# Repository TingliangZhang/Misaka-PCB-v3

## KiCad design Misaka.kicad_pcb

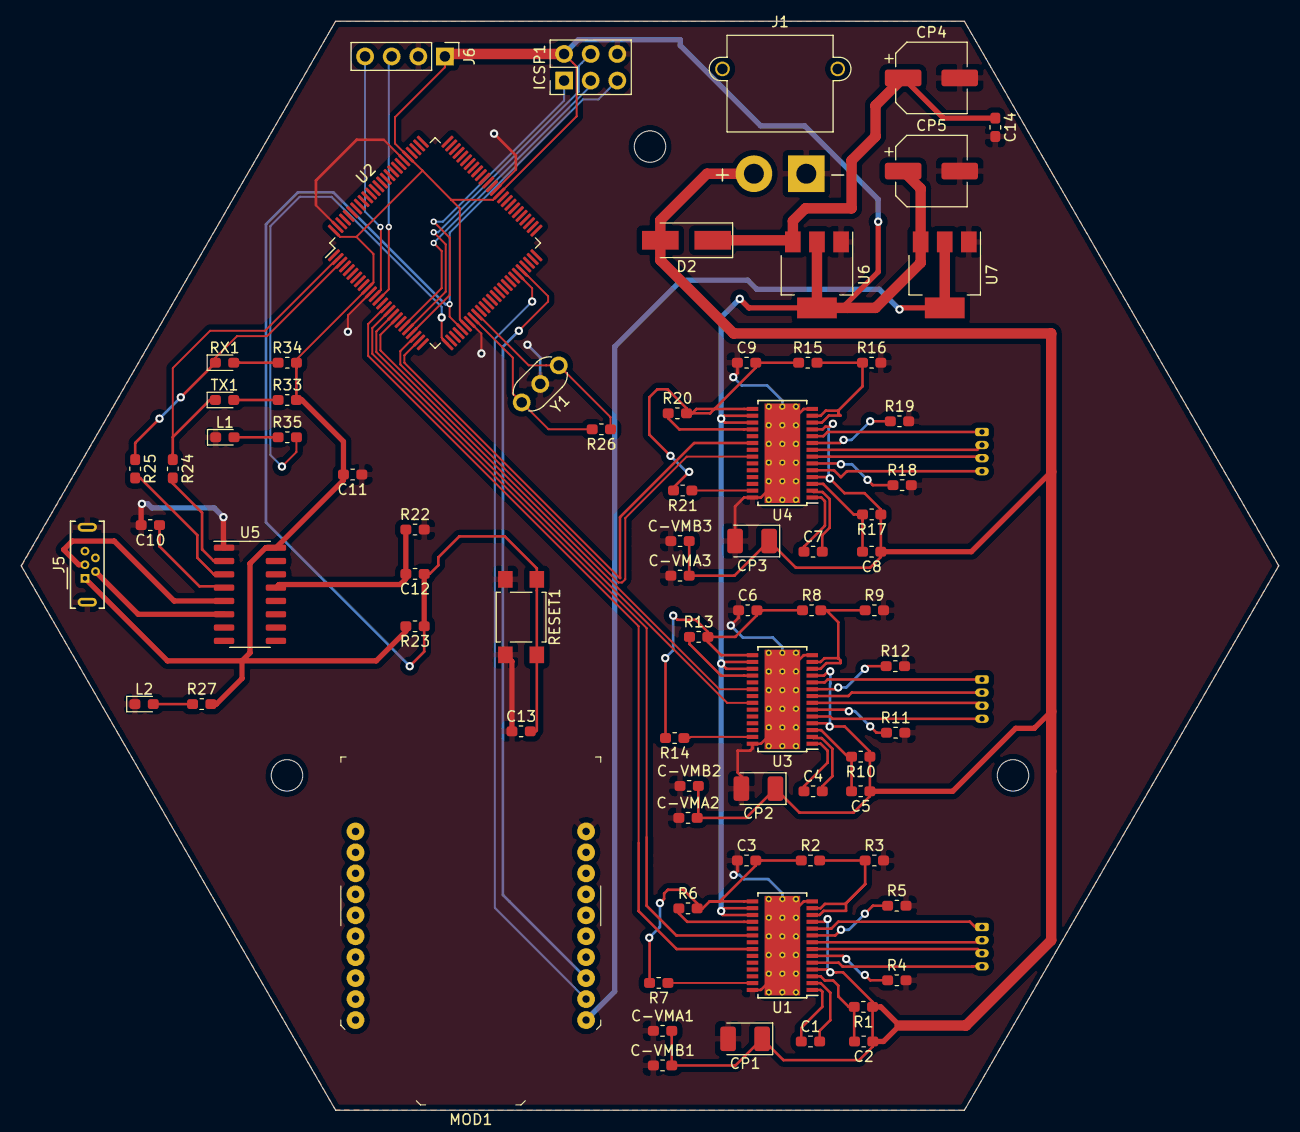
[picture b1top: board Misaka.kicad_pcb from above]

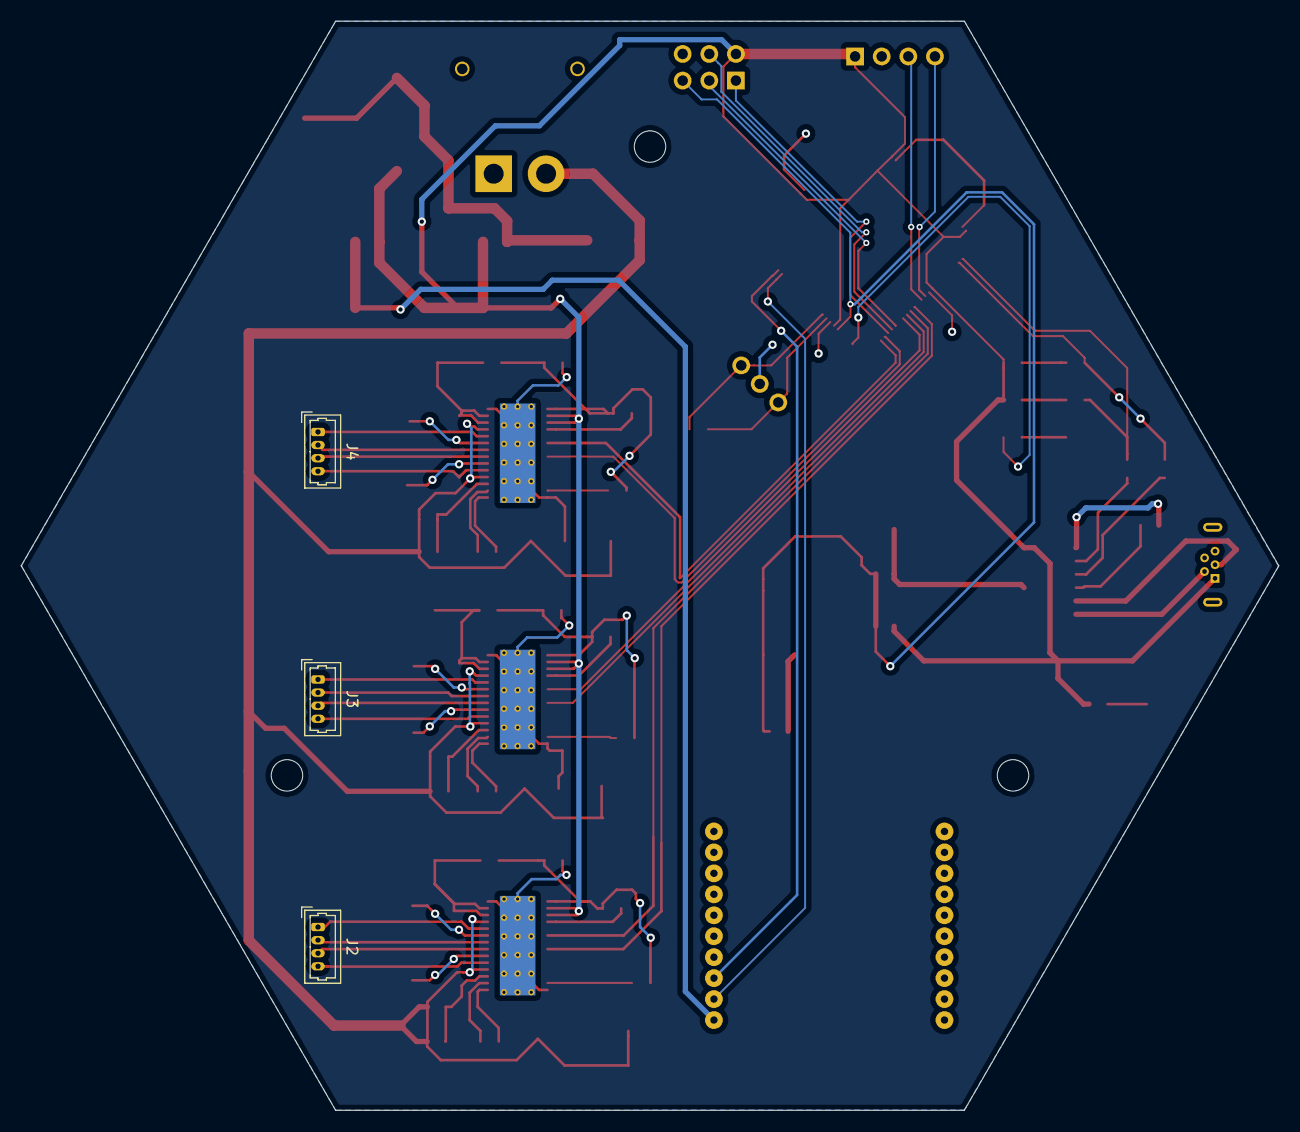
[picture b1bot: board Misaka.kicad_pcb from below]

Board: 2 copper layers, 120.0 x 103.9 mm, 77 parts (3 on the bottom side), 73 nets.

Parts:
C1, C4, C7: 0.01uF; C_0603_1608Metric_Pad1.05x0.95mm_HandSolder
C2, C5, C8: 0.1uF; C_0603_1608Metric_Pad1.05x0.95mm_HandSolder
C3, C6, C9: 0.47uF; C_0603_1608Metric_Pad1.05x0.95mm_HandSolder
C10, C11, C12, C14: 100nF; C_0603_1608Metric_Pad1.05x0.95mm_HandSolder
C13: 22pF; C_0603_1608Metric_Pad1.05x0.95mm_HandSolder
C-VMA1, C-VMA2, C-VMA3: 0.1uF; C_0603_1608Metric_Pad1.05x0.95mm_HandSolder
C-VMB1, C-VMB2, C-VMB3: 0.1uF; C_0603_1608Metric_Pad1.05x0.95mm_HandSolder
CP1, CP2, CP3: 100uF; CP_EIA-3528-21_Kemet-B_Pad1.50x2.35mm_HandSolder
CP4, CP5: 47uF; CP_Elec_6.3x5.8
D2: M7; D_SMA_Handsoldering
ICSP1: Conn_02x03_Odd_Even; PinHeader_2x03_P2.54mm_Vertical
J1: Battery; AMASS_XT30PW-M_1x02_P2.50mm_Horizontal
J2, J3, J4: Conn_01x04_Male; Molex_PicoBlade_53047-0410_1x04_P1.25mm_Vertical
J5: USB_B_Micro; USB_Micro-B_Wuerth_614105150721_Vertical
J6: Conn_01x04_Female; PinHeader_1x04_P2.54mm_Vertical
L1, L2: LED; LED_0603_1608Metric_Pad1.05x0.95mm_HandSolder
MOD1: XB24CZ7PIT-004; XBEE_PRO-20_THT
R1, R10, R17, R26: 1M; R_0603_1608Metric_Pad1.05x0.95mm_HandSolder
R2, R8, R15: 50K; R_0603_1608Metric_Pad1.05x0.95mm_HandSolder
R3, R9, R16: 30K; R_0603_1608Metric_Pad1.05x0.95mm_HandSolder
R4, R5, R11, R12, R18, R19: 200m; R_0603_1608Metric_Pad1.05x0.95mm_HandSolder
R6, R7, R13, R14, R20, R21: 10K; R_0603_1608Metric_Pad1.05x0.95mm_HandSolder
R22, R24, R25, R27, R33, R34, R35: 1k; R_0603_1608Metric_Pad1.05x0.95mm_HandSolder
R23: 10k; R_0603_1608Metric_Pad1.05x0.95mm_HandSolder
RESET1: SW_Push; SW_SPST_TL3305A
RX1: LED; LED_0603_1608Metric_Pad1.05x0.95mm_HandSolder
TX1: LED; LED_0603_1608Metric_Pad1.05x0.95mm_HandSolder
U1, U3, U4: DRV8825PWPR; HTSSOP-28-1EP_4.4x9.7mm_P0.65mm_EP3.4x9.5mm_ThermalVias
U2: ATmega2560-16AU; TQFP-100_14x14mm_P0.5mm
U5: CH340C; SOIC-16_3.9x9.9mm_P1.27mm
U6: AMS1117-5.0; SOT-223-3_TabPin2
U7: AMS1117-3.3; SOT-223-3_TabPin2
Y1: CSTLS16M0X51-B0; Resonator_muRata_CSTLSxxxX-3Pin_W5.5mm_H3.0mm

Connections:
+3V3: MOD1.1, U7.2
+5V: C11.2, CP5.1, ICSP1.2, J5.1, J6.1, R23.2, R27.2, R33.2, R34.2, U1.16, U1.17, U2.10, U2.31, U2.61, U2.80, U2.100, U3.16, U3.17, U4.16, U4.17, U5.16, U6.2, U7.3
+12V: C2.1, C5.1, C8.1, C-VMA1.2, C-VMA2.2, C-VMA3.2, C-VMB1.2, C-VMB2.2, C-VMB3.2, CP1.1, CP2.1, CP3.1, D2.2, J1.2, R1.1, R10.1, R17.1, U1.4, U1.11, U3.4, U3.11, U4.4, U4.11
/D6: U1.22, U2.15
/D7: U1.20, U2.16
/D8: U2.17, U3.22
/D9: U2.18, U3.20
/D10: U2.23, U4.22
/D11: U2.24, U4.20
/D13: R35.2, U2.26
/MISO: ICSP1.1, U2.22
/MOSI: ICSP1.4, U2.21
/RESET: C12.1, C13.2, ICSP1.5, R23.1, RESET1.1, U2.30
/RX0: R24.1, TX1.1, U2.2
/RX1: MOD1.2, U2.45
/RX2: J6.4, U2.12
/SCK: ICSP1.3, U2.20
/StepperMotorDriver1/V3P3OUT: C3.2, R2.1, R6.2, R7.2, U1.15
/StepperMotorDriver2/V3P3OUT: C6.2, R8.1, R13.2, R14.2, U3.15
/StepperMotorDriver3/V3P3OUT: C9.2, R15.1, R20.2, R21.2, U4.15
/TX0: R25.1, RX1.1, U2.3
/TX1: MOD1.3, U2.46
/TX2: J6.3, U2.13
GND: C3.1, C6.1, C9.1, C10.2, C11.1, C13.1, C14.2, C-VMA1.1, C-VMA2.1, C-VMA3.1, C-VMB1.1, C-VMB2.1, C-VMB3.1, CP1.2, CP2.2, CP3.2, CP4.2, CP5.2, ICSP1.6, J1.1, J5.5, J5.6, J6.2, L1.1, L2.1, MOD1.10, R3.2, R4.2, R5.2, R9.2, R11.2, R12.2, R16.2, R18.2, R19.2, R22.2, RESET1.2, U1.14, U1.28, U1.29, U2.11, U2.32, U2.62, U2.81, U2.99, U3.14, U3.28, U3.29, U4.14, U4.28, U4.29, U5.1, U6.1, U7.1, Y1.2
unnamed: C1.1, U1.1
unnamed: C1.2, U1.2
unnamed: C2.2, R1.2, U1.3
unnamed: C4.1, U3.1
unnamed: C4.2, U3.2
unnamed: C5.2, R10.2, U3.3
unnamed: C7.1, U4.1
unnamed: C7.2, U4.2
unnamed: C8.2, R17.2, U4.3
unnamed: C10.1, U5.4
unnamed: C12.2, R22.1, U5.13
unnamed: C14.1, CP4.1, D2.1, U6.3
unnamed: J2.1, U1.10
unnamed: J2.2, U1.8
unnamed: J2.3, U1.7
unnamed: J2.4, U1.5
unnamed: J3.1, U3.10
unnamed: J3.2, U3.8
unnamed: J3.3, U3.7
unnamed: J3.4, U3.5
unnamed: J4.1, U4.10
unnamed: J4.2, U4.8
unnamed: J4.3, U4.7
unnamed: J4.4, U4.5
unnamed: J5.2, U5.6
unnamed: J5.3, U5.5
unnamed: L1.2, R35.1
unnamed: L2.2, R27.1
unnamed: R2.2, R3.1, U1.12, U1.13
unnamed: R4.1, U1.6
unnamed: R5.1, U1.9
unnamed: R6.1, U1.18
unnamed: R7.1, U1.27
unnamed: R8.2, R9.1, U3.12, U3.13
unnamed: R11.1, U3.6
unnamed: R12.1, U3.9
unnamed: R13.1, U3.18
unnamed: R14.1, U3.27
unnamed: R15.2, R16.1, U4.12, U4.13
unnamed: R18.1, U4.6
unnamed: R19.1, U4.9
unnamed: R20.1, U4.18
unnamed: R21.1, U4.27
unnamed: R24.2, U5.2
unnamed: R25.2, U5.3
unnamed: R26.1, U2.34, Y1.1
unnamed: R26.2, U2.33, Y1.3
unnamed: R33.1, TX1.2
unnamed: R34.1, RX1.2

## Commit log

2020-04-11 ImportFromV2
2020-04-11 DEL-CH340C-UNNEC
2020-04-11 RX-TX0
2020-04-11 BATTERY FLIP
2020-04-11 Test Pin
2020-04-11 DEL Camera
2020-04-11 DEL LED MS123
2020-04-11 except GND
2020-04-11 gerber
2020-04-12 v3.1
2020-04-15 ibom
